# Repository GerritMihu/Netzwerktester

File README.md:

# Netzwerktester
 Diskreter Netzwerkkabeltester mit BC846

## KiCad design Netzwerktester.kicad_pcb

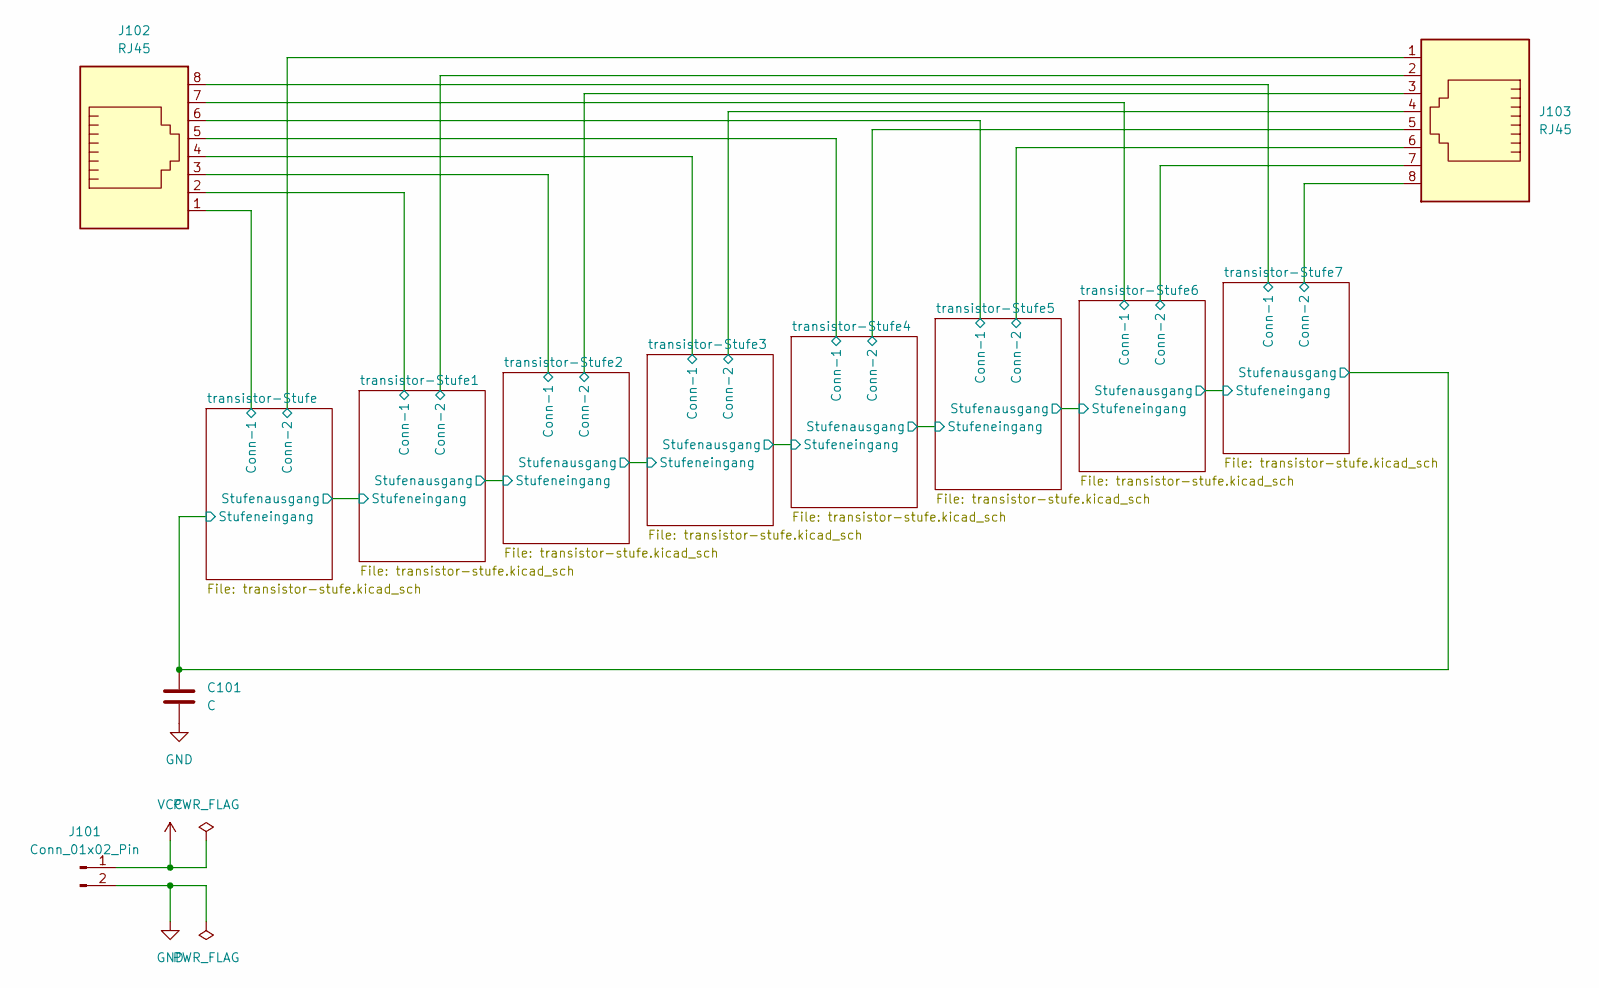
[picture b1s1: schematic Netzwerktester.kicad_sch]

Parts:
C101: C; C_0805_2012Metric_Pad1.18x1.45mm_HandSolder
J101: Conn_01x02_Pin; PinHeader_1x02_P2.54mm_Vertical
J102, J103: RJ45; RJ45_Molex_0855135013_Vertical

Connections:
/transistor-Stufe1/Conn-1: J102.2; also elsewhere on the board
/transistor-Stufe1/Conn-2: J103.2; also elsewhere on the board
/transistor-Stufe2/Conn-1: J102.3; also elsewhere on the board
/transistor-Stufe2/Conn-2: J103.3; also elsewhere on the board
/transistor-Stufe3/Conn-1: J102.4; also elsewhere on the board
/transistor-Stufe3/Conn-2: J103.4; also elsewhere on the board
/transistor-Stufe4/Conn-1: J102.5; also elsewhere on the board
/transistor-Stufe4/Conn-2: J103.5; also elsewhere on the board
/transistor-Stufe5/Conn-1: J102.6; also elsewhere on the board
/transistor-Stufe5/Conn-2: J103.6; also elsewhere on the board
/transistor-Stufe6/Conn-1: J102.7; also elsewhere on the board
/transistor-Stufe6/Conn-2: J103.7; also elsewhere on the board
/transistor-Stufe7/Conn-1: J102.8; also elsewhere on the board
/transistor-Stufe7/Conn-2: J103.8; also elsewhere on the board
/transistor-Stufe/Conn-1: J102.1; also elsewhere on the board
/transistor-Stufe/Conn-2: J103.1; also elsewhere on the board
/transistor-Stufe/Stufeneingang: C101.1; also elsewhere on the board
GND: C101.2, J101.2; also elsewhere on the board
VCC: J101.1; also elsewhere on the board

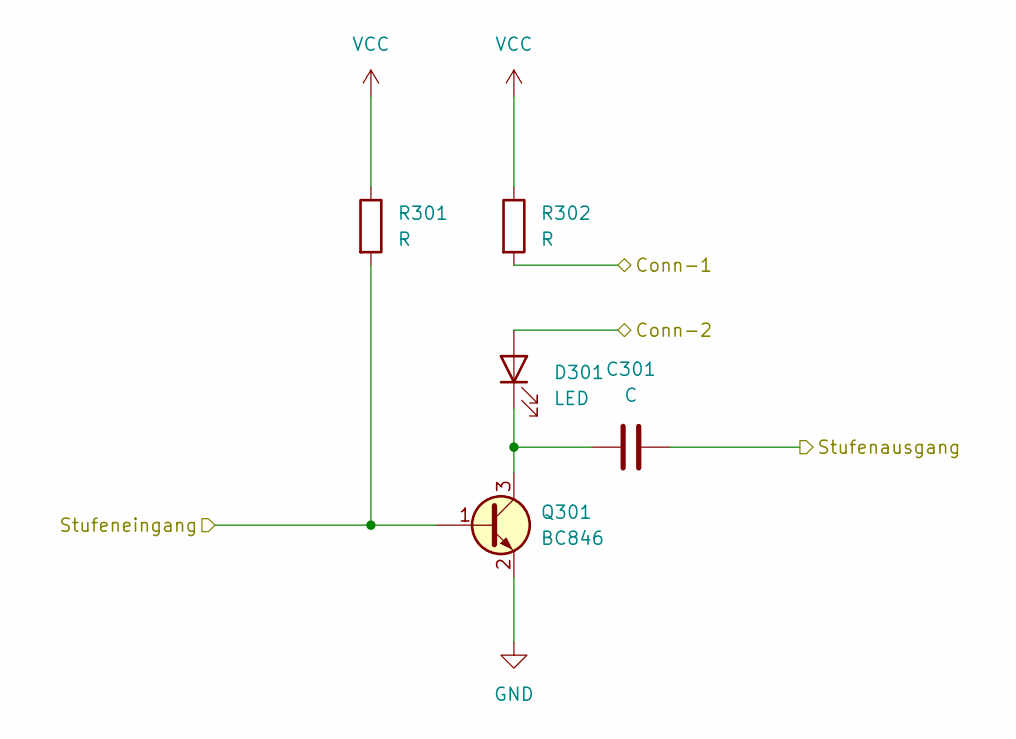
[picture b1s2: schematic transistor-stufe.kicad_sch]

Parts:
C301: C; C_0805_2012Metric_Pad1.18x1.45mm_HandSolder
D301: LED; LED_0805_2012Metric_Pad1.15x1.40mm_HandSolder
Q301: BC846; SOT-23
R301, R302: R; R_0805_2012Metric_Pad1.20x1.40mm_HandSolder

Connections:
/transistor-Stufe1/Conn-1: R302.2; also elsewhere on the board
/transistor-Stufe1/Conn-2: D301.2 (A); also elsewhere on the board
/transistor-Stufe1/Stufenausgang: C301.2; also elsewhere on the board
/transistor-Stufe/Stufenausgang: Q301.1 (B), R301.2; also elsewhere on the board
GND: Q301.2 (E); also elsewhere on the board
unnamed: C301.1, D301.1 (K), Q301.3 (C)
VCC: R301.1, R302.1; also elsewhere on the board

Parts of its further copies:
C201, C401, C501, C601, C701, C801, C901: C; C_0805_2012Metric_Pad1.18x1.45mm_HandSolder
D201, D401, D501, D601, D701, D801, D901: LED; LED_0805_2012Metric_Pad1.15x1.40mm_HandSolder
Q201, Q401, Q501, Q601, Q701, Q801, Q901: BC846; SOT-23
R201, R202, R401, R402, R501, R502, R601, R602, R701, R702, R801, R802, R901, R902: R; R_0805_2012Metric_Pad1.20x1.40mm_HandSolder

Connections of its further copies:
/transistor-Stufe1/Stufenausgang: Q401.1 (B), R401.2; also elsewhere on the board
/transistor-Stufe2/Conn-1: R402.2; also elsewhere on the board
/transistor-Stufe2/Conn-2: D401.2 (A); also elsewhere on the board
/transistor-Stufe2/Stufenausgang: C401.2, Q501.1 (B), R501.2
/transistor-Stufe3/Conn-1: R502.2; also elsewhere on the board
/transistor-Stufe3/Conn-2: D501.2 (A); also elsewhere on the board
/transistor-Stufe3/Stufenausgang: C501.2, Q601.1 (B), R601.2
/transistor-Stufe4/Conn-1: R602.2; also elsewhere on the board
/transistor-Stufe4/Conn-2: D601.2 (A); also elsewhere on the board
/transistor-Stufe4/Stufenausgang: C601.2, Q701.1 (B), R701.2
/transistor-Stufe5/Conn-1: R702.2; also elsewhere on the board
/transistor-Stufe5/Conn-2: D701.2 (A); also elsewhere on the board
/transistor-Stufe5/Stufenausgang: C701.2, Q801.1 (B), R801.2
/transistor-Stufe6/Conn-1: R802.2; also elsewhere on the board
/transistor-Stufe6/Conn-2: D801.2 (A); also elsewhere on the board
/transistor-Stufe6/Stufenausgang: C801.2, Q901.1 (B), R901.2
/transistor-Stufe7/Conn-1: R902.2; also elsewhere on the board
/transistor-Stufe7/Conn-2: D901.2 (A); also elsewhere on the board
/transistor-Stufe/Conn-1: R202.2; also elsewhere on the board
/transistor-Stufe/Conn-2: D201.2 (A); also elsewhere on the board
/transistor-Stufe/Stufenausgang: C201.2; also elsewhere on the board
/transistor-Stufe/Stufeneingang: C901.2, Q201.1 (B), R201.2; also elsewhere on the board
GND: Q201.2 (E), Q401.2 (E), Q501.2 (E), Q601.2 (E), Q701.2 (E), Q801.2 (E), Q901.2 (E); also elsewhere on the board
unnamed: C201.1, D201.1 (K), Q201.3 (C)
unnamed: C401.1, D401.1 (K), Q401.3 (C)
unnamed: C501.1, D501.1 (K), Q501.3 (C)
unnamed: C601.1, D601.1 (K), Q601.3 (C)
unnamed: C701.1, D701.1 (K), Q701.3 (C)
unnamed: C801.1, D801.1 (K), Q801.3 (C)
unnamed: C901.1, D901.1 (K), Q901.3 (C)
VCC: R201.1, R202.1, R401.1, R402.1, R501.1, R502.1, R601.1, R602.1, R701.1, R702.1, R801.1, R802.1, R901.1, R902.1; also elsewhere on the board

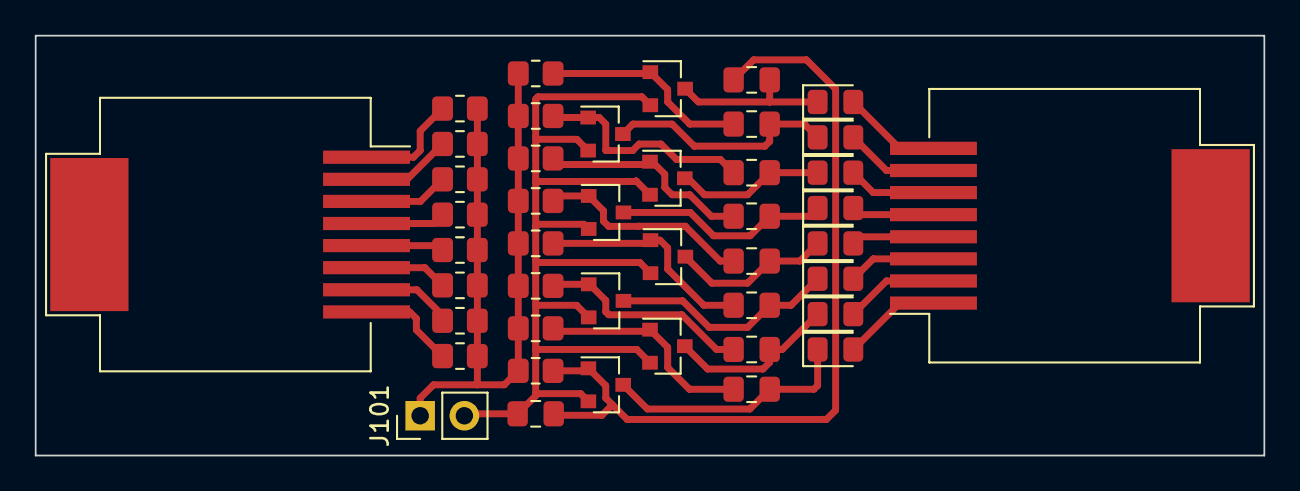
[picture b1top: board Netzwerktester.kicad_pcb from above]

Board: 2 copper layers, 70.6 x 24.1 mm, 44 parts (0 on the bottom side), 34 nets.
